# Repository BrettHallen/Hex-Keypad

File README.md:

# Hex Keypad
A simple keypad for Arduino using Cherrry MX type key switches.<br>

The main idea was so I could test keyboard scan codes using an Arduino as a protocol converter.<br>

It's pretty simple:
- no diodes to prevent ghosting - expects only one key at a time
- no pull-up resistors - activate in Arduino

Needs nine pins on the Arduino - five for rows and four for columns.<br>

- Enter the two digit hex code, 0x00 to 0xFF
- Press ENTER when the number entry is completed
- Press INVERT if you want to invert the entered hex value, i.e. ~0x12 = 0xED
- Press CLEAR if you make a mistake and want to reset the entry
- Press SEND to instruct the Arduino to send the scan code to the host computer

## [KiCad Design & Fabrication Files](/KiCad)
Schematic, PCB and Gerber files.<br>

## [Arduino Sketch]
To be done

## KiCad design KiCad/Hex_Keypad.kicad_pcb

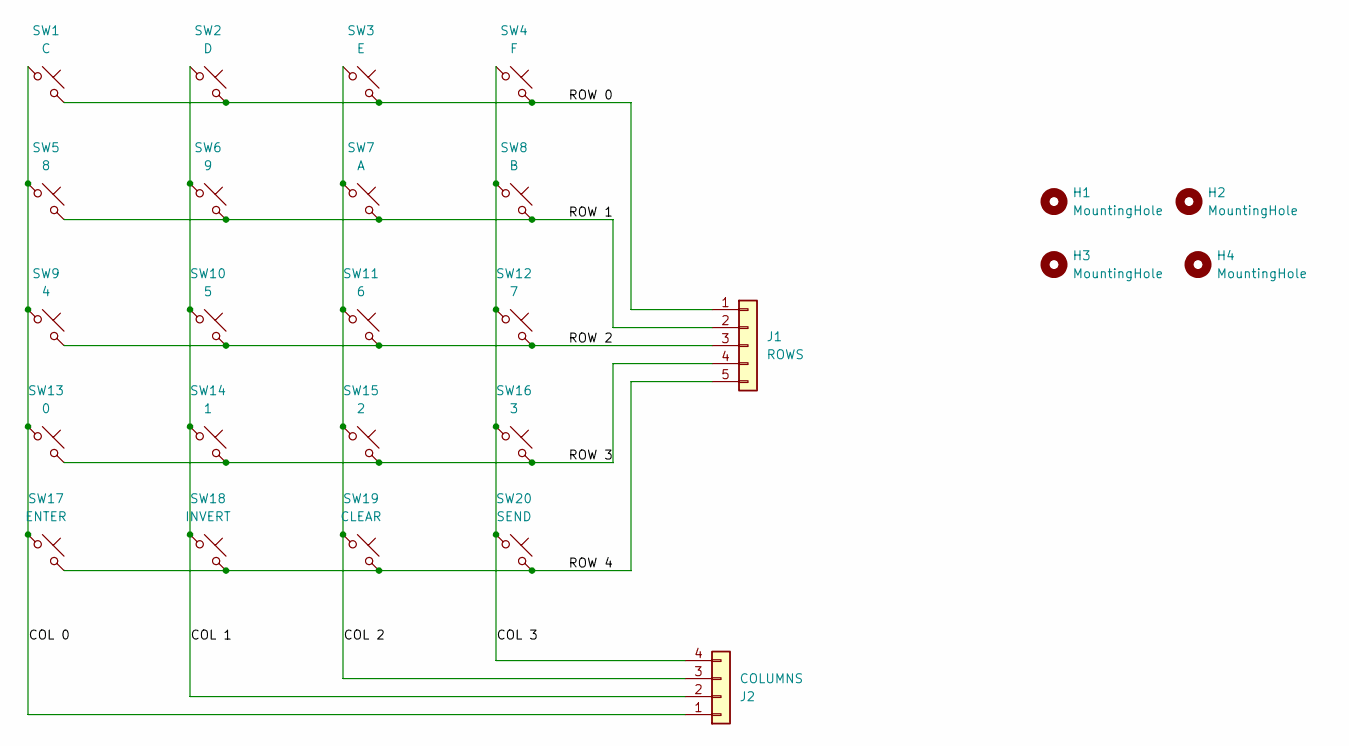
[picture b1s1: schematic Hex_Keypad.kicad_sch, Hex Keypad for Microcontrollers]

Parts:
H1, H2, H3, H4: MountingHole; MountingHole_3.2mm_M3
J1: ROWS; PinHeader_1x05_P2.54mm_Vertical
J2: COLUMNS; PinHeader_1x04_P2.54mm_Vertical
SW1: C; SW_Cherry_MX_PCB_1.00u
SW2: D; SW_Cherry_MX_PCB_1.00u
SW3: E; SW_Cherry_MX_PCB_1.00u
SW4: F; SW_Cherry_MX_PCB_1.00u
SW5: 8; SW_Cherry_MX_PCB_1.00u
SW6: 9; SW_Cherry_MX_PCB_1.00u
SW7: A; SW_Cherry_MX_PCB_1.00u
SW8: B; SW_Cherry_MX_PCB_1.00u
SW9: 4; SW_Cherry_MX_PCB_1.00u
SW10: 5; SW_Cherry_MX_PCB_1.00u
SW11: 6; SW_Cherry_MX_PCB_1.00u
SW12: 7; SW_Cherry_MX_PCB_1.00u
SW13: 0; SW_Cherry_MX_PCB_1.00u
SW14: 1; SW_Cherry_MX_PCB_1.00u
SW15: 2; SW_Cherry_MX_PCB_1.00u
SW16: 3; SW_Cherry_MX_PCB_1.00u
SW17: ENTER; SW_Cherry_MX_PCB_1.00u
SW18: INVERT; SW_Cherry_MX_PCB_1.00u
SW19: CLEAR; SW_Cherry_MX_PCB_1.00u
SW20: SEND; SW_Cherry_MX_PCB_1.00u

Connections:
/COL 0: J2.1, SW1.1, SW5.1, SW9.1, SW13.1, SW17.1
/COL 1: J2.2, SW2.1, SW6.1, SW10.1, SW14.1, SW18.1
/COL 2: J2.3, SW3.1, SW7.1, SW11.1, SW15.1, SW19.1
/COL 3: J2.4, SW4.1, SW8.1, SW12.1, SW16.1, SW20.1
/ROW 0: J1.1, SW1.2, SW2.2, SW3.2, SW4.2
/ROW 1: J1.2, SW5.2, SW6.2, SW7.2, SW8.2
/ROW 2: J1.3, SW9.2, SW10.2, SW11.2, SW12.2
/ROW 3: J1.4, SW13.2, SW14.2, SW15.2, SW16.2
/ROW 4: J1.5, SW17.2, SW18.2, SW19.2, SW20.2

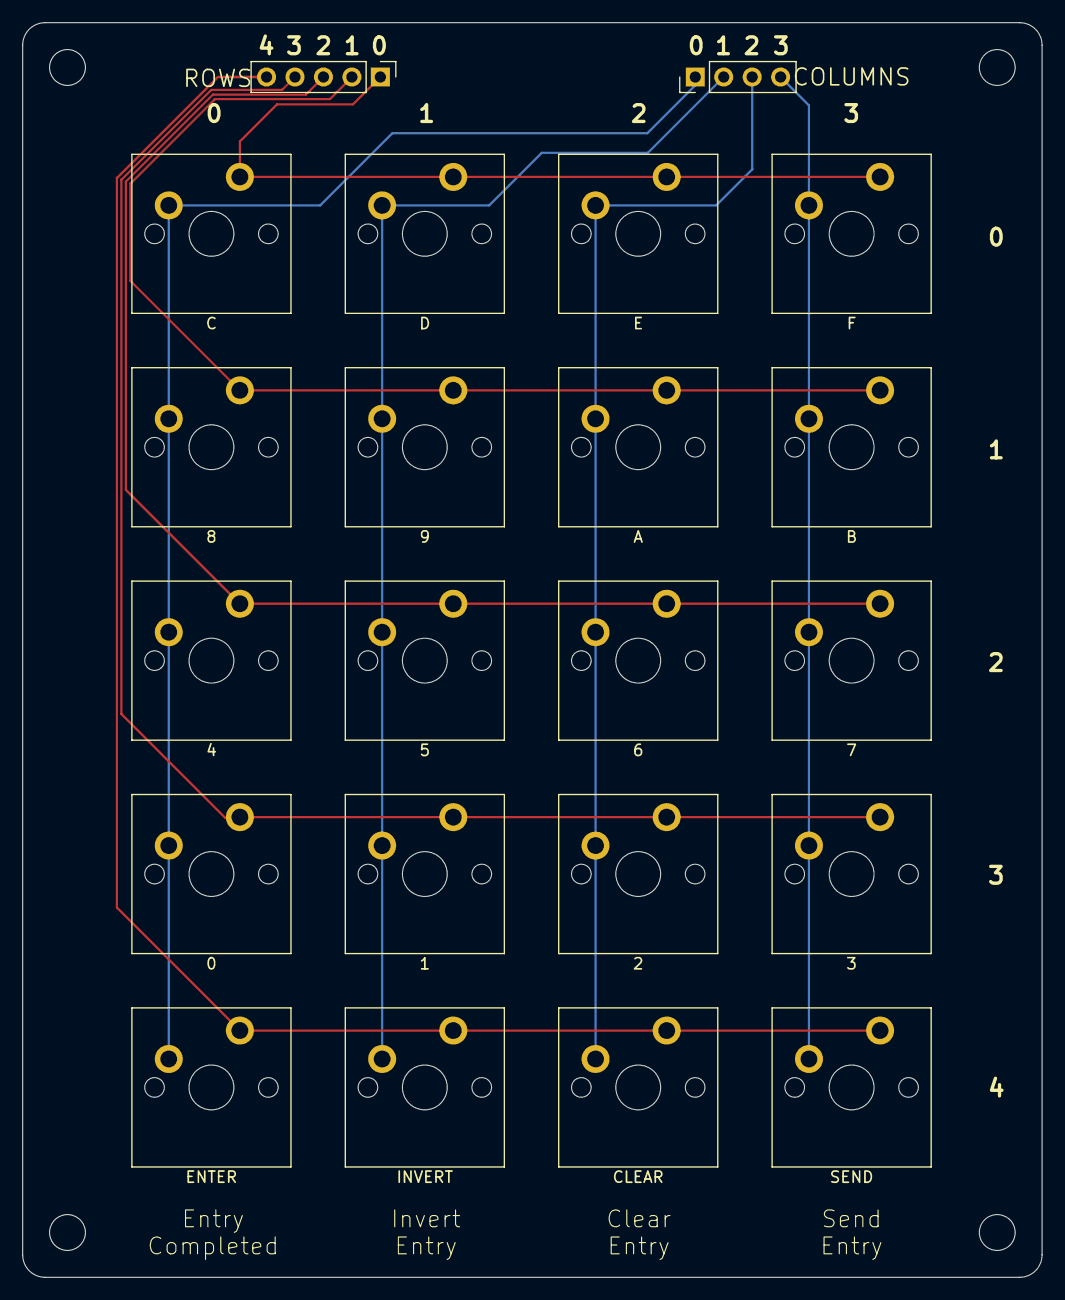
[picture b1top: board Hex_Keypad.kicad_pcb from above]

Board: 2 copper layers, 91.0 x 112.0 mm, 26 parts (0 on the bottom side), 9 nets.

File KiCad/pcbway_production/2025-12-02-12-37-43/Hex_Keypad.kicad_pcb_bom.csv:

Designator,Quantity,Value,Footprint,Package,MPN,DNP,Mount_Type,Description
J1,1,ROWS,PinHeader_1x05_P2.54mm_Vertical,,,,tht,"Generic connector, single row, 01x05, script generated (kicad-library-utils/schlib/autogen/connector/)"
J2,1,COLUMNS,PinHeader_1x04_P2.54mm_Vertical,,,,tht,"Generic connector, single row, 01x04, script generated (kicad-library-utils/schlib/autogen/connector/)"
SW1,1,C,SW_Cherry_MX_PCB_1.00u,,,,tht,"Push button switch, normally open, two pins, 45° tilted"
SW10,1,5,SW_Cherry_MX_PCB_1.00u,,,,tht,"Push button switch, normally open, two pins, 45° tilted"
SW11,1,6,SW_Cherry_MX_PCB_1.00u,,,,tht,"Push button switch, normally open, two pins, 45° tilted"
SW12,1,7,SW_Cherry_MX_PCB_1.00u,,,,tht,"Push button switch, normally open, two pins, 45° tilted"
SW13,1,0,SW_Cherry_MX_PCB_1.00u,,,,tht,"Push button switch, normally open, two pins, 45° tilted"
SW14,1,1,SW_Cherry_MX_PCB_1.00u,,,,tht,"Push button switch, normally open, two pins, 45° tilted"
SW15,1,2,SW_Cherry_MX_PCB_1.00u,,,,tht,"Push button switch, normally open, two pins, 45° tilted"
SW16,1,3,SW_Cherry_MX_PCB_1.00u,,,,tht,"Push button switch, normally open, two pins, 45° tilted"
SW17,1,ENTER,SW_Cherry_MX_PCB_1.00u,,,,tht,"Push button switch, normally open, two pins, 45° tilted"
SW18,1,INVERT,SW_Cherry_MX_PCB_1.00u,,,,tht,"Push button switch, normally open, two pins, 45° tilted"
SW19,1,CLEAR,SW_Cherry_MX_PCB_1.00u,,,,tht,"Push button switch, normally open, two pins, 45° tilted"
SW2,1,D,SW_Cherry_MX_PCB_1.00u,,,,tht,"Push button switch, normally open, two pins, 45° tilted"
SW20,1,SEND,SW_Cherry_MX_PCB_1.00u,,,,tht,"Push button switch, normally open, two pins, 45° tilted"
SW3,1,E,SW_Cherry_MX_PCB_1.00u,,,,tht,"Push button switch, normally open, two pins, 45° tilted"
SW4,1,F,SW_Cherry_MX_PCB_1.00u,,,,tht,"Push button switch, normally open, two pins, 45° tilted"
SW5,1,8,SW_Cherry_MX_PCB_1.00u,,,,tht,"Push button switch, normally open, two pins, 45° tilted"
SW6,1,9,SW_Cherry_MX_PCB_1.00u,,,,tht,"Push button switch, normally open, two pins, 45° tilted"
SW7,1,A,SW_Cherry_MX_PCB_1.00u,,,,tht,"Push button switch, normally open, two pins, 45° tilted"
SW8,1,B,SW_Cherry_MX_PCB_1.00u,,,,tht,"Push button switch, normally open, two pins, 45° tilted"
SW9,1,4,SW_Cherry_MX_PCB_1.00u,,,,tht,"Push button switch, normally open, two pins, 45° tilted"
